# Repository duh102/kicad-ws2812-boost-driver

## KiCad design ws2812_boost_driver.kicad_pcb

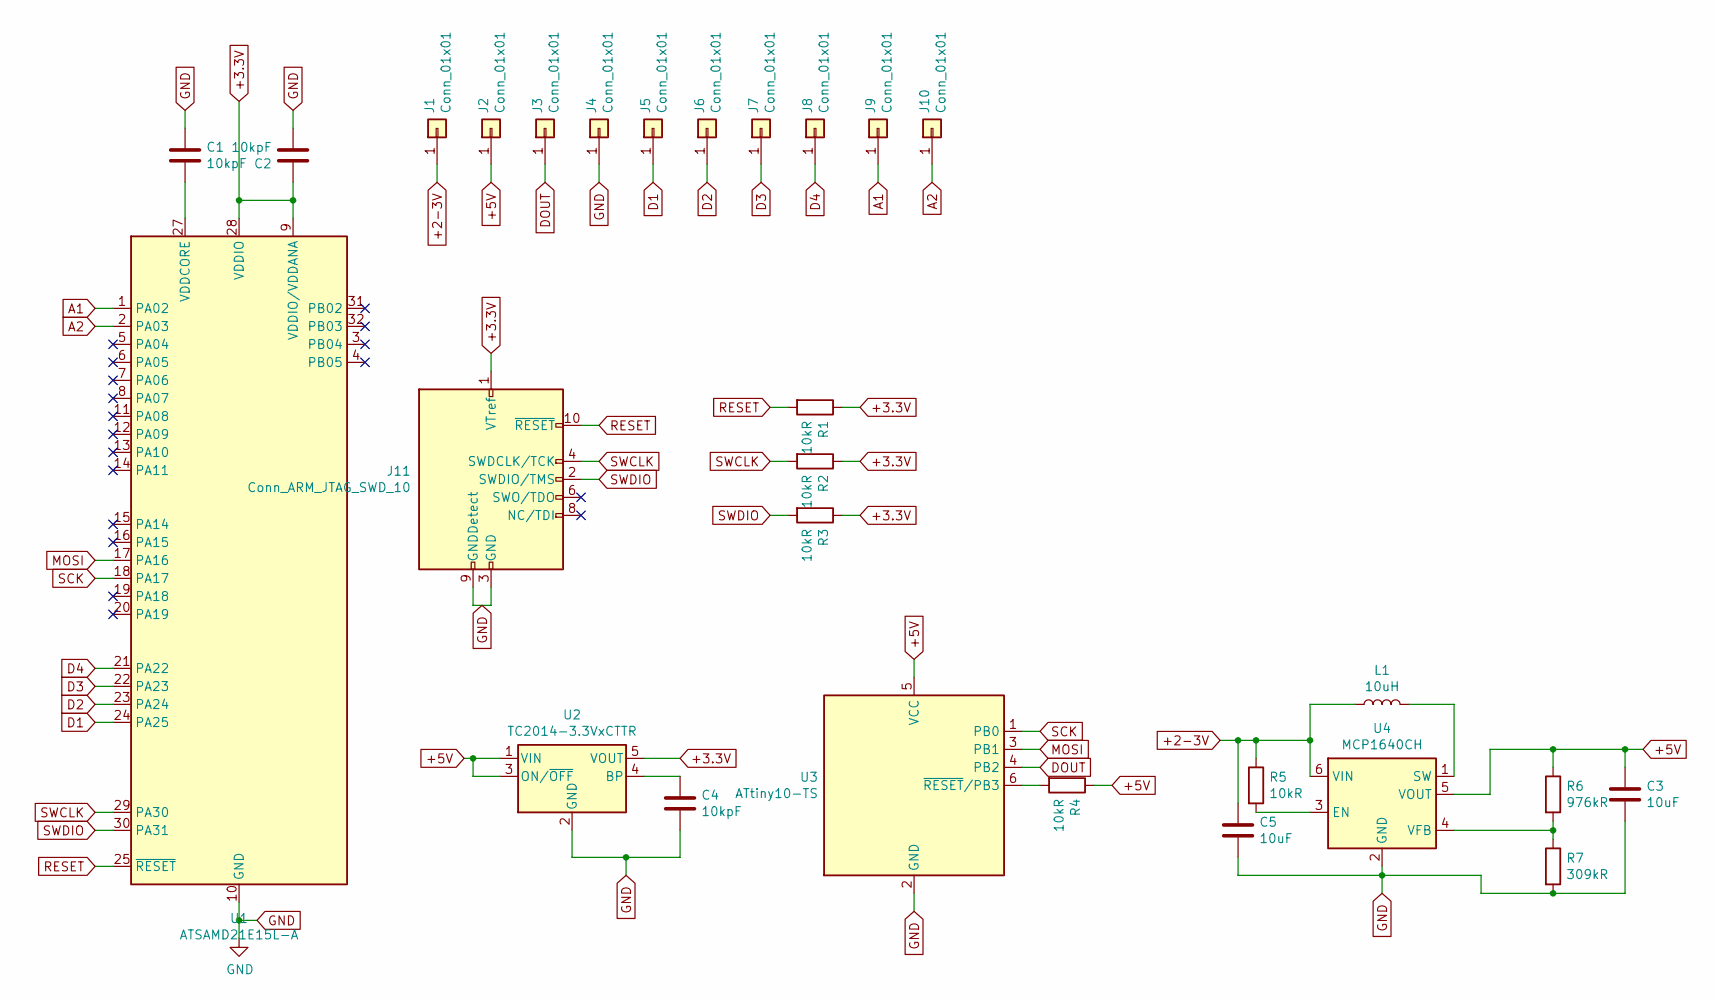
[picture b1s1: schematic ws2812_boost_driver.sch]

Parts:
C1, C2, C4: 10kpF; C_0603_1608Metric
C3, C5: 10uF; C_0805_2012Metric
J1, J2, J3, J4, J5, J6, J7, J8, J9, J10: Conn_01x01; TestPoint_Pad_1.5x1.5mm
J11: Conn_ARM_JTAG_SWD_10; PinHeader_2x05_P1.27mm_Vertical
L1: 10uH; L_Taiyo-Yuden_NR-50xx
R1, R2, R3, R4, R5: 10kR; R_0805_2012Metric
R6: 976kR; R_0805_2012Metric
R7: 309kR; R_0805_2012Metric
U1: ATSAMD21E15L-A; TQFP-32_7x7mm_P0.8mm
U2: TC2014-3.3VxCTTR; SOT-23-5
U3: ATtiny10-TS; SOT-23-6
U4: MCP1640CH; SOT-23-6

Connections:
+2-3V: C5.1, J1.1, L1.1, R5.1, U4.6 (VIN)
+3.3V: C2.1, J11.1 (VTref), R1.1, R2.1, R3.1, U1.9 (VDDIO/VDDANA), U1.28 (VDDIO), U2.5 (VOUT)
+5V: C3.1, J2.1, R4.1, R6.1, U2.1 (VIN), U2.3 (ON/~OFF~), U3.5 (VCC), U4.5 (VOUT)
A1: J9.1, U1.1 (PA02)
A2: J10.1, U1.2 (PA03)
D1: J5.1, U1.24 (PA25)
D2: J6.1, U1.23 (PA24)
D3: J7.1, U1.22 (PA23)
D4: J8.1, U1.21 (PA22)
DOUT: J3.1, U3.4 (PB2)
GND: C1.1, C2.2, C3.2, C4.2, C5.2, J4.1, J11.3 (GND), J11.5 (GND), J11.9 (GNDDetect), R7.2, U1.10 (GND), U1.26 (GND), U2.2 (GND), U3.2 (GND), U4.2 (GND)
MOSI: U1.17 (PA16), U3.3 (PB1)
unnamed: C1.2, U1.27 (VDDCORE)
unnamed: C4.1, U2.4 (BP)
unnamed: L1.2, U4.1 (SW)
unnamed: R4.2, U3.6 (~RESET~/PB3)
unnamed: R5.2, U4.3 (EN)
unnamed: R6.2, R7.1, U4.4 (VFB)
RESET: J11.10 (~RESET~), R1.2, U1.25 (~RESET)
SCK: U1.18 (PA17), U3.1 (PB0)
SWCLK: J11.4 (SWDCLK/TCK), R2.2, U1.29 (PA30)
SWDIO: J11.2 (SWDIO/TMS), R3.2, U1.30 (PA31)

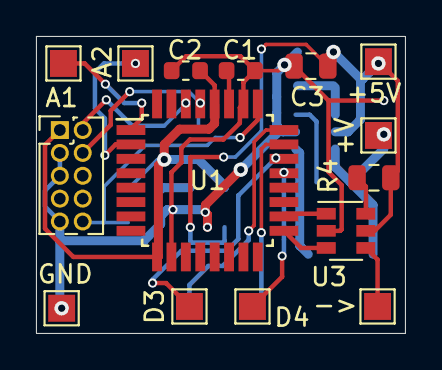
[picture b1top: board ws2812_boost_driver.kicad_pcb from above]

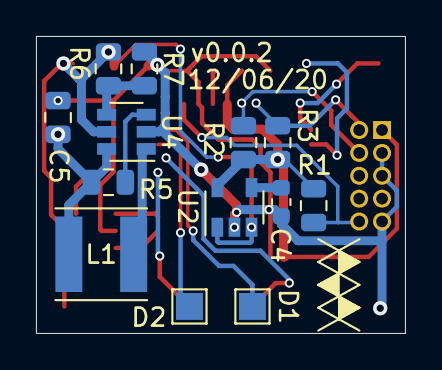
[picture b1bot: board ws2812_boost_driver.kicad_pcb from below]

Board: 2 copper layers, 20.5 x 16.5 mm, 28 parts (13 on the bottom side), 22 nets.

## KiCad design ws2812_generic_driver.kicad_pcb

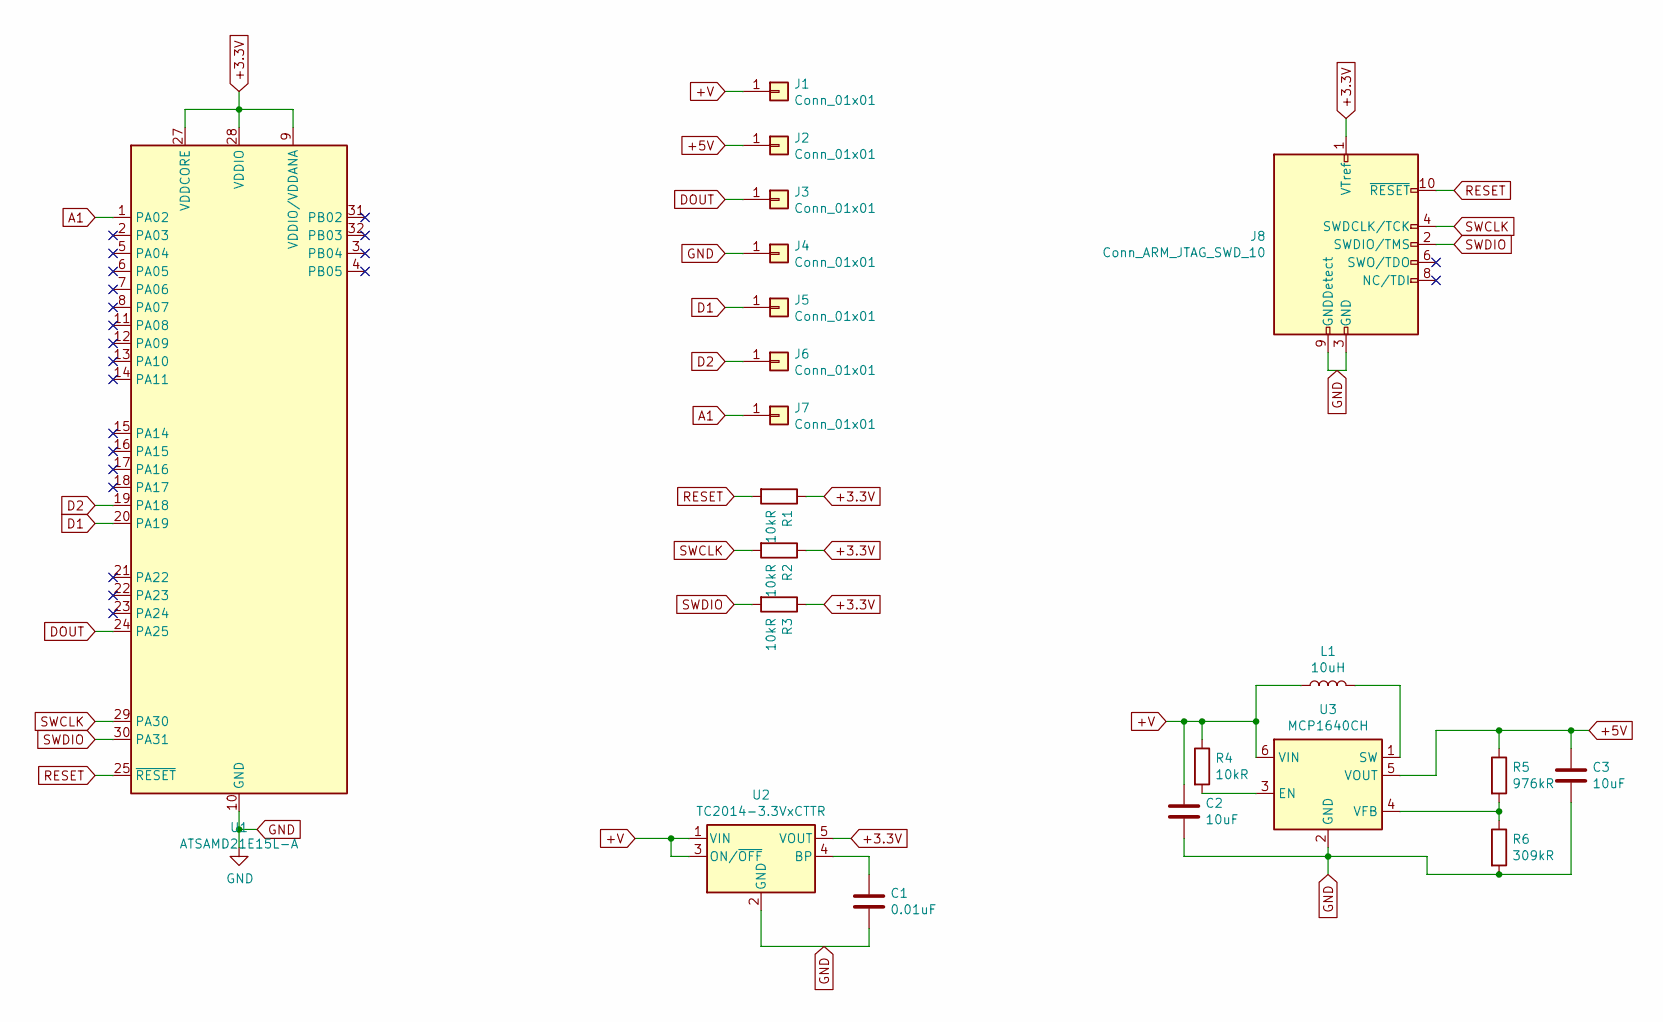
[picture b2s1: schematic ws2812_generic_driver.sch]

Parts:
C1: 0.01uF; C_0603_1608Metric
C2, C3: 10uF; C_0603_1608Metric
J1, J2, J3, J4, J5, J6, J7: Conn_01x01; TestPoint_Pad_1.5x1.5mm
J8: Conn_ARM_JTAG_SWD_10; PinHeader_2x05_P1.00mm_Vertical
L1: 10uH; L_Taiyo-Yuden_NR-50xx
R1, R2, R3, R4: 10kR; R_0805_2012Metric
R5: 976kR; R_0805_2012Metric
R6: 309kR; R_0805_2012Metric
U1: ATSAMD21E15L-A; TQFP-32_7x7mm_P0.8mm
U2: TC2014-3.3VxCTTR; SOT-23-5
U3: MCP1640CH; SOT-23-6

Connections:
+3.3V: J8.1 (VTref), R1.1, R2.1, R3.1, U1.9 (VDDIO/VDDANA), U1.27 (VDDCORE), U1.28 (VDDIO), U2.5 (VOUT)
+5V: C3.1, J2.1, R5.1, U3.5 (VOUT)
+V: C2.1, J1.1, L1.1, R4.1, U2.1 (VIN), U2.3 (ON/~OFF~), U3.6 (VIN)
A1: J7.1, U1.1 (PA02)
D1: J5.1, U1.20 (PA19)
D2: J6.1, U1.19 (PA18)
DOUT: J3.1, U1.24 (PA25)
GND: C1.2, C2.2, C3.2, J4.1, J8.3 (GND), J8.5 (GND), J8.9 (GNDDetect), R6.2, U1.10 (GND), U1.26 (GND), U2.2 (GND), U3.2 (GND)
unnamed: C1.1, U2.4 (BP)
unnamed: L1.2, U3.1 (SW)
unnamed: R4.2, U3.3 (EN)
unnamed: R5.2, R6.1, U3.4 (VFB)
RESET: J8.10 (~RESET~), R1.2, U1.25 (~RESET)
SWCLK: J8.4 (SWDCLK/TCK), R2.2, U1.29 (PA30)
SWDIO: J8.2 (SWDIO/TMS), R3.2, U1.30 (PA31)

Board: 2 copper layers, 21 parts (0 on the bottom side), 15 nets, no tracks yet.

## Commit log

2020-11-11 Unfinished board
2020-11-12 Finish PCB
2020-11-12 Fix project filenames
2020-11-14 Add attiny10 hardware spi->ws2812 support
2020-11-14 Update 3d model for render
2020-12-07 Fix core vreg issue
